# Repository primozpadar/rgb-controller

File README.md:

# RGB Controller CLI

## CLI Usage

### Install (with cargo)

```
cargo install --path="."
```

## Communication protocol

```
structure: |<channel>|<r>|<g>|<b>|
           |         |   |   |   |
bytes:     |   <1>   |<1>|<1>|<1>|
```

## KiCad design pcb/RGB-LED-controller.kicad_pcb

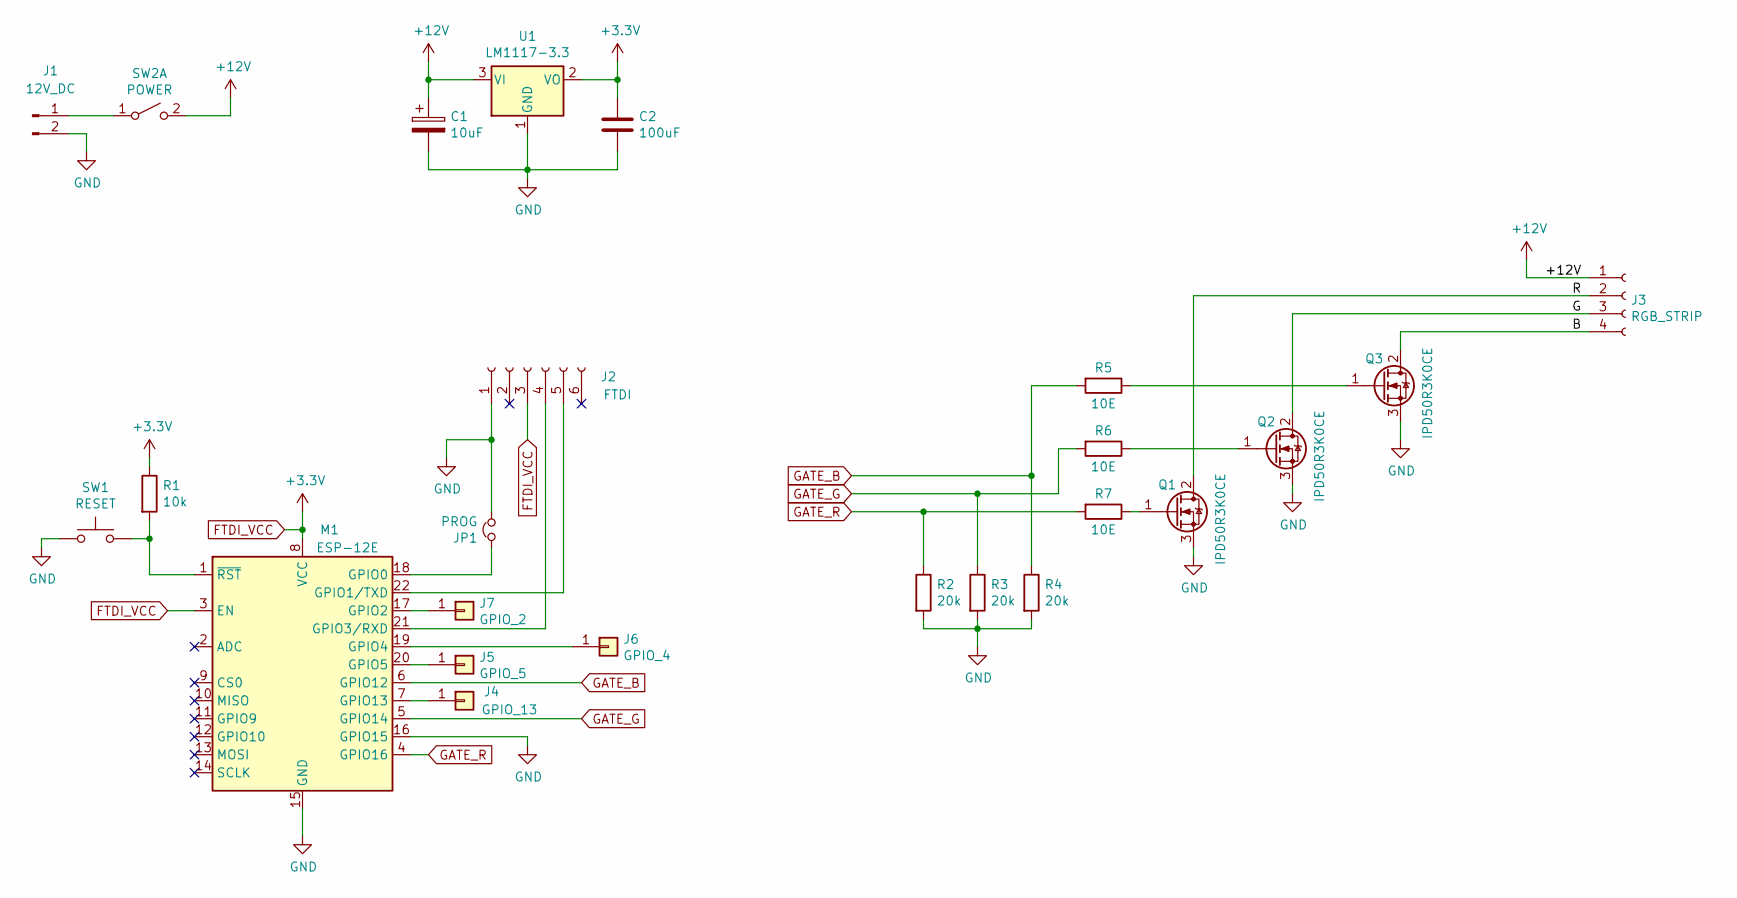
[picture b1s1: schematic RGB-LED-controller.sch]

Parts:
C1: 10uF
C2: 100uF
J1: 12V_DC; BarrelJack_Horizontal
J2: FTDI; PinSocket_1x06_P2.54mm_Vertical
J3: RGB_STRIP; PinSocket_1x04_P2.54mm_Vertical
J4: GPIO_13; PinSocket_1x01_P2.54mm_Vertical
J5: GPIO_5; PinSocket_1x01_P2.54mm_Vertical
J6: GPIO_4; PinSocket_1x01_P2.54mm_Vertical
J7: GPIO_2; PinSocket_1x01_P2.54mm_Vertical
JP1: PROG; PinHeader_1x02_P2.54mm_Vertical
M1: ESP-12E
Q1, Q2, Q3: IPD50R3K0CE; TO-252-2
R1: 10k; R_0402_1005Metric
R2, R3, R4: 20k; R_0603_1608Metric_Pad1.05x0.95mm_HandSolder
R5, R6, R7: 10E; R_0402_1005Metric
SW1: RESET; SW_DIP_SPSTx01_Slide_6.7x4.1mm_W8.61mm_P2.54mm_LowProfile
SW2: POWER; PinHeader_1x02_P2.54mm_Vertical
U1: LM1117-3.3; SOT-223-3_TabPin2

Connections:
+12V: C1.1, J3.1, SW2.2 (B), U1.3 (VI)
/B: J3.4, Q3.2 (D)
/G: J3.3, Q2.2 (D)
/R: J3.2, Q1.2 (D)
FTDI_VCC: C2.1, J2.3, M1.3 (EN), M1.8 (VCC), R1.1, U1.2 (VO)
GATE_B: M1.6 (GPIO12), R4.1, R5.2
GATE_G: M1.5 (GPIO14), R3.1, R6.2
GATE_R: M1.4 (GPIO16), R2.1, R7.2
GND: C1.2, C2.2, J1.2, J2.1, JP1.2, M1.15 (GND), M1.16 (GPIO15), Q1.3 (S), Q2.3 (S), Q3.3 (S), R2.2, R3.2, R4.2, SW1.1, U1.1 (GND)
unnamed: J1.1, SW2.1 (A)
unnamed: J2.4, M1.21 (GPIO3/RXD)
unnamed: J2.5, M1.22 (GPIO1/TXD)
unnamed: J4.1, M1.7 (GPIO13)
unnamed: J5.1, M1.20 (GPIO5)
unnamed: J6.1, M1.19 (GPIO4)
unnamed: J7.1, M1.17 (GPIO2)
unnamed: JP1.1, M1.18 (GPIO0)
unnamed: M1.1 (~RST), R1.2, SW1.2
unnamed: Q1.1 (G), R7.1
unnamed: Q2.1 (G), R6.1
unnamed: Q3.1 (G), R5.1

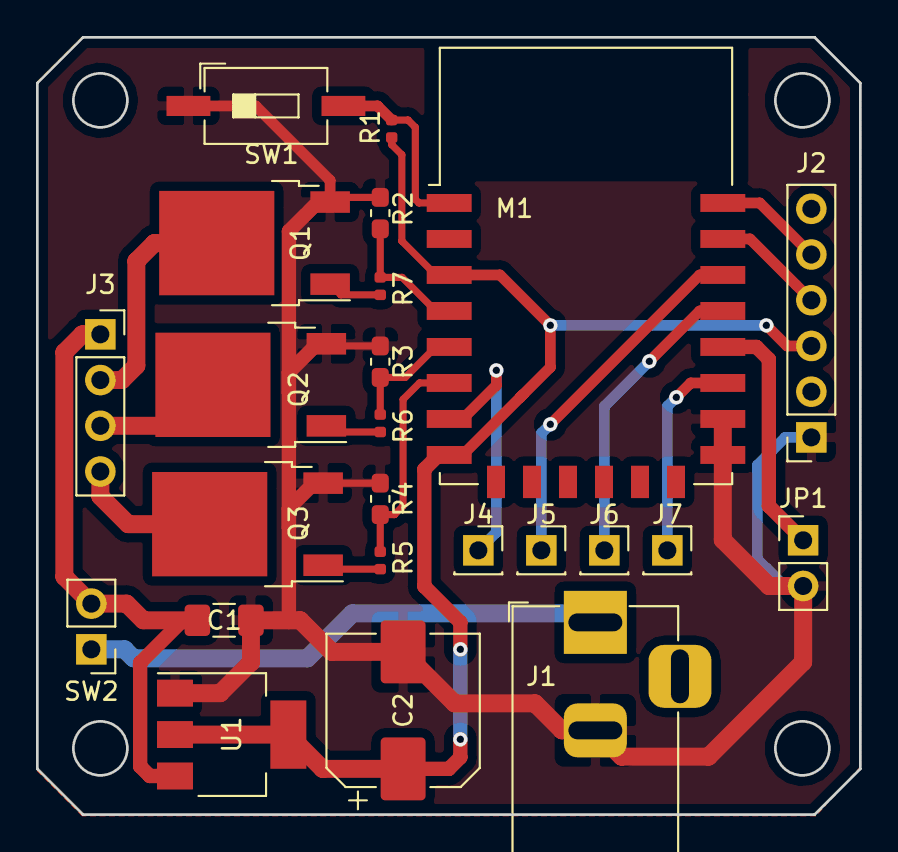
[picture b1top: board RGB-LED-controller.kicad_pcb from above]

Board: 2 copper layers, 45.7 x 43.2 mm, 24 parts (0 on the bottom side), 21 nets.

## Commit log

2022-01-22 late initial commit 😅
2022-01-23 desktop app
2022-01-30 cli basic commands
2022-01-30 add formatting + default device id
2022-01-30 show default id command
2022-01-31 add presets
2022-02-01 rename cli to rgb
2022-03-29 fix config path
2022-03-29 print config
2022-03-29 print help
2024-01-05 expo app
2024-01-08 move to app dir
2024-01-08 push notifications
2024-04-26 update firmware, CLI and app to support multiple groups & no broadcast
2024-04-27 install to ios device
